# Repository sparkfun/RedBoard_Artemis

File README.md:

SparkFun RedBoard Artemis
============================

[*SparkFun RedBoard (DEV-15444)*](https://www.sparkfun.com/products/15444)

Think of the RedBoard Artemis as just another Arduino... That has BLE. And one meg of flash. And runs at less than 1mA. Oh, and it can run TensorFlow models. Ya, that too. The RedBoard Artemis takes the incredibly powerful Artemis module from SparkFun and wraps it up in an easy to use and familiar Uno footprint. We've written an Arduino core from scratch to make programming the Artemis as familiar as `Serial.begin(9600)`. Time-to-first-blink is less than five minutes.

The RedBoard Artemis has the improved power conditioning and USB to serial that we've refined over the years on our RedBoard line of products. A modern USB-C connector makes programming easy. A Qwiic connector makes I<sup>2</sup>C easy. The RedBoard Artemis is fully compatible with SparkFun's Arduino core and can be programmed easily under the Arduino IDE. We've exposed the JTAG connector for more advanced users who prefer to use the power and speed of professional tools. We've added a digital MEMS microphone for folks wanting to experiment with always-on voice commands with TensorFlow and machine learning. We've even added a convenient jumper to measure current consumption for low power testing.

With 1M flash and 384k RAM you'll have plenty of room for your sketches. The Artemis module runs at 48MHz with a 96MHz turbo mode available and with Bluetooth to boot!

The SparkFun RedBoard Artemis is a great platform to 'kick the tires' of this amazing module. If you're interesting in testing out the full capabilities of the SparkFun Artemis module or if you're looking for more compact solution, be sure to checkout our ATP and Nano versions of the Artemis line.

Repository Contents
-------------------
* **/Hardware** - Eagle design files (.brd, .sch)

Documentation
-------------------
* **[Hookup Guide for the RedBoard Artemis](https://learn.sparkfun.com/tutorials/hookup-guide-for-the-sparkfun-redboard-artemis)**
* **[Artemis Development with Arduino](https://learn.sparkfun.com/tutorials/artemis-development-with-arduino)**
* **[Ambiq Apollo3 SDK SetUp](https://learn.sparkfun.com/tutorials/using-sparkfun-edge-board-with-ambiq-apollo3-sdk)**
* **[Designing with the SparkFun Artemis](https://learn.sparkfun.com/tutorials/designing-with-the-sparkfun-artemis)**
* **[CH340E USB to serial IC Drivers](https://www.sparkfun.com/ch340)**

License Information
-------------------

This product is _**open source**_! 

Please review the LICENSE.md file for license information. 

If you have any questions or concerns on licensing, please contact techsupport@sparkfun.com.

Please use, reuse, and modify these files as you see fit. Please maintain attribution to SparkFun Electronics and release any derivative under the same license.

Distributed as-is; no warranty is given.

- Your friends at SparkFun.

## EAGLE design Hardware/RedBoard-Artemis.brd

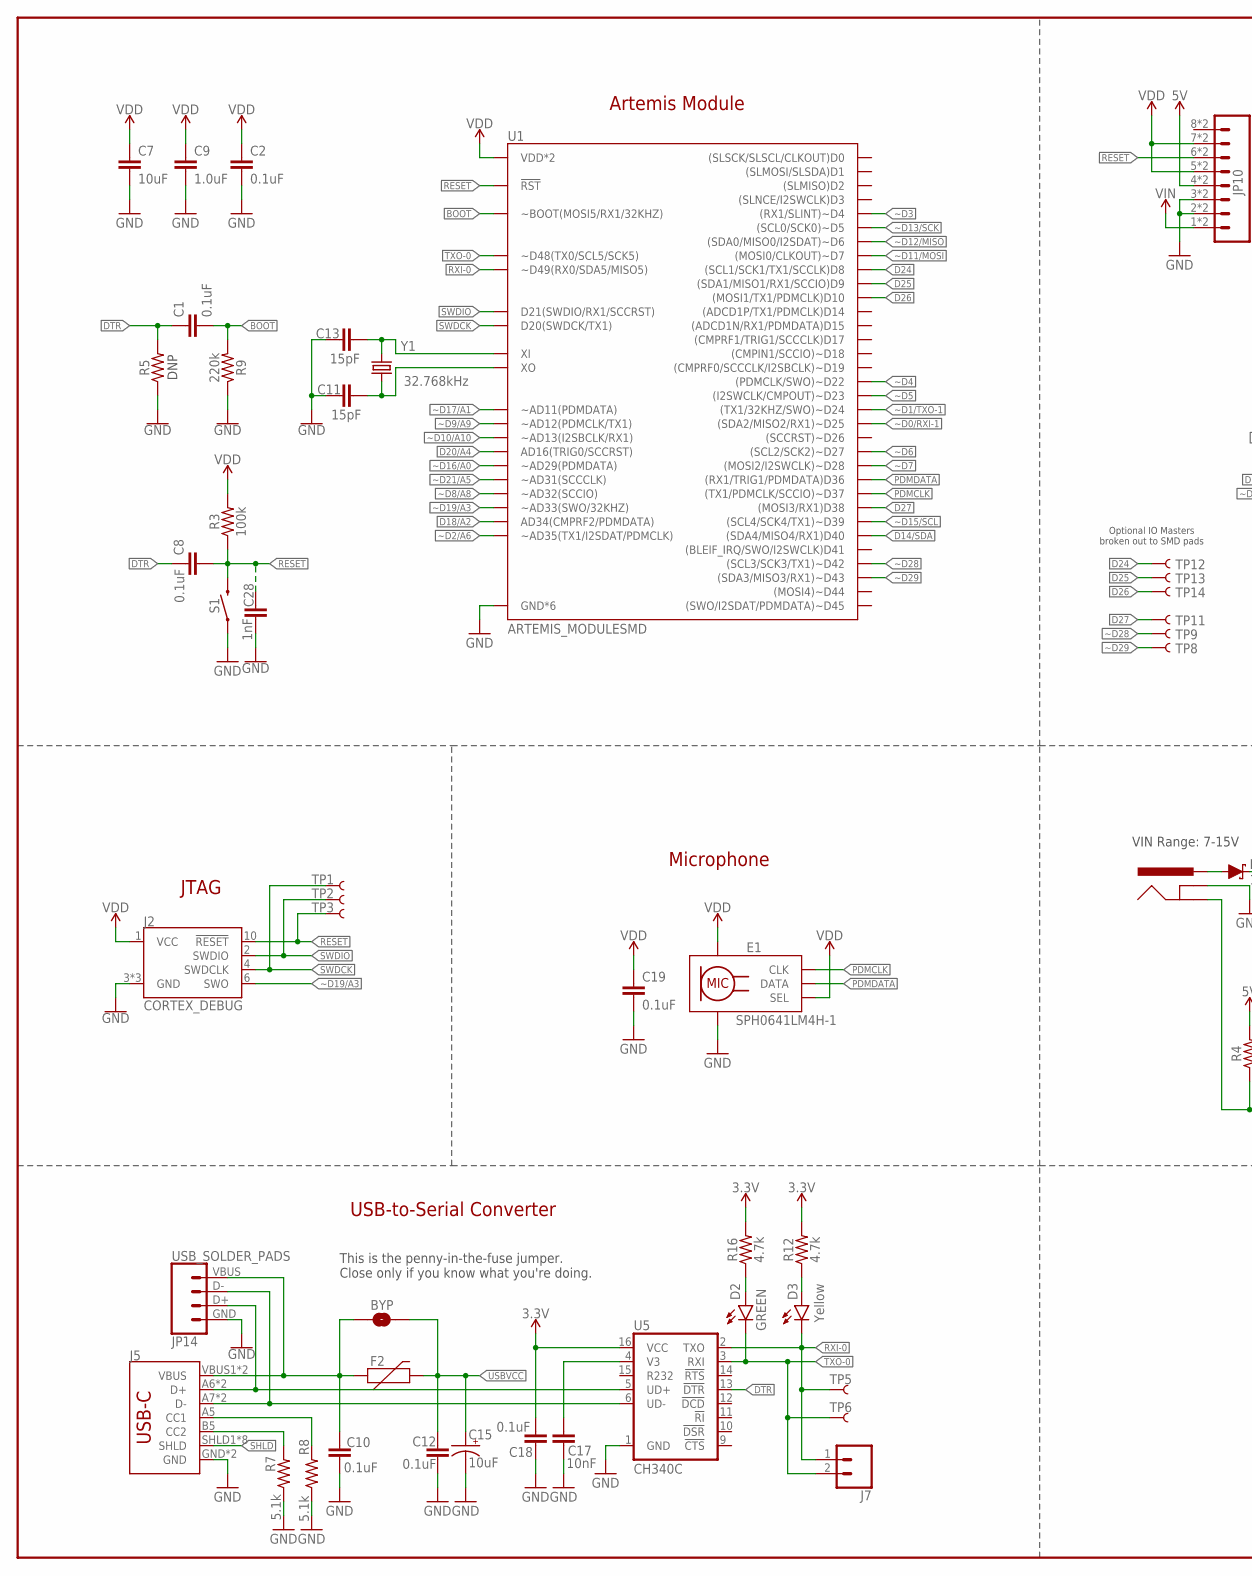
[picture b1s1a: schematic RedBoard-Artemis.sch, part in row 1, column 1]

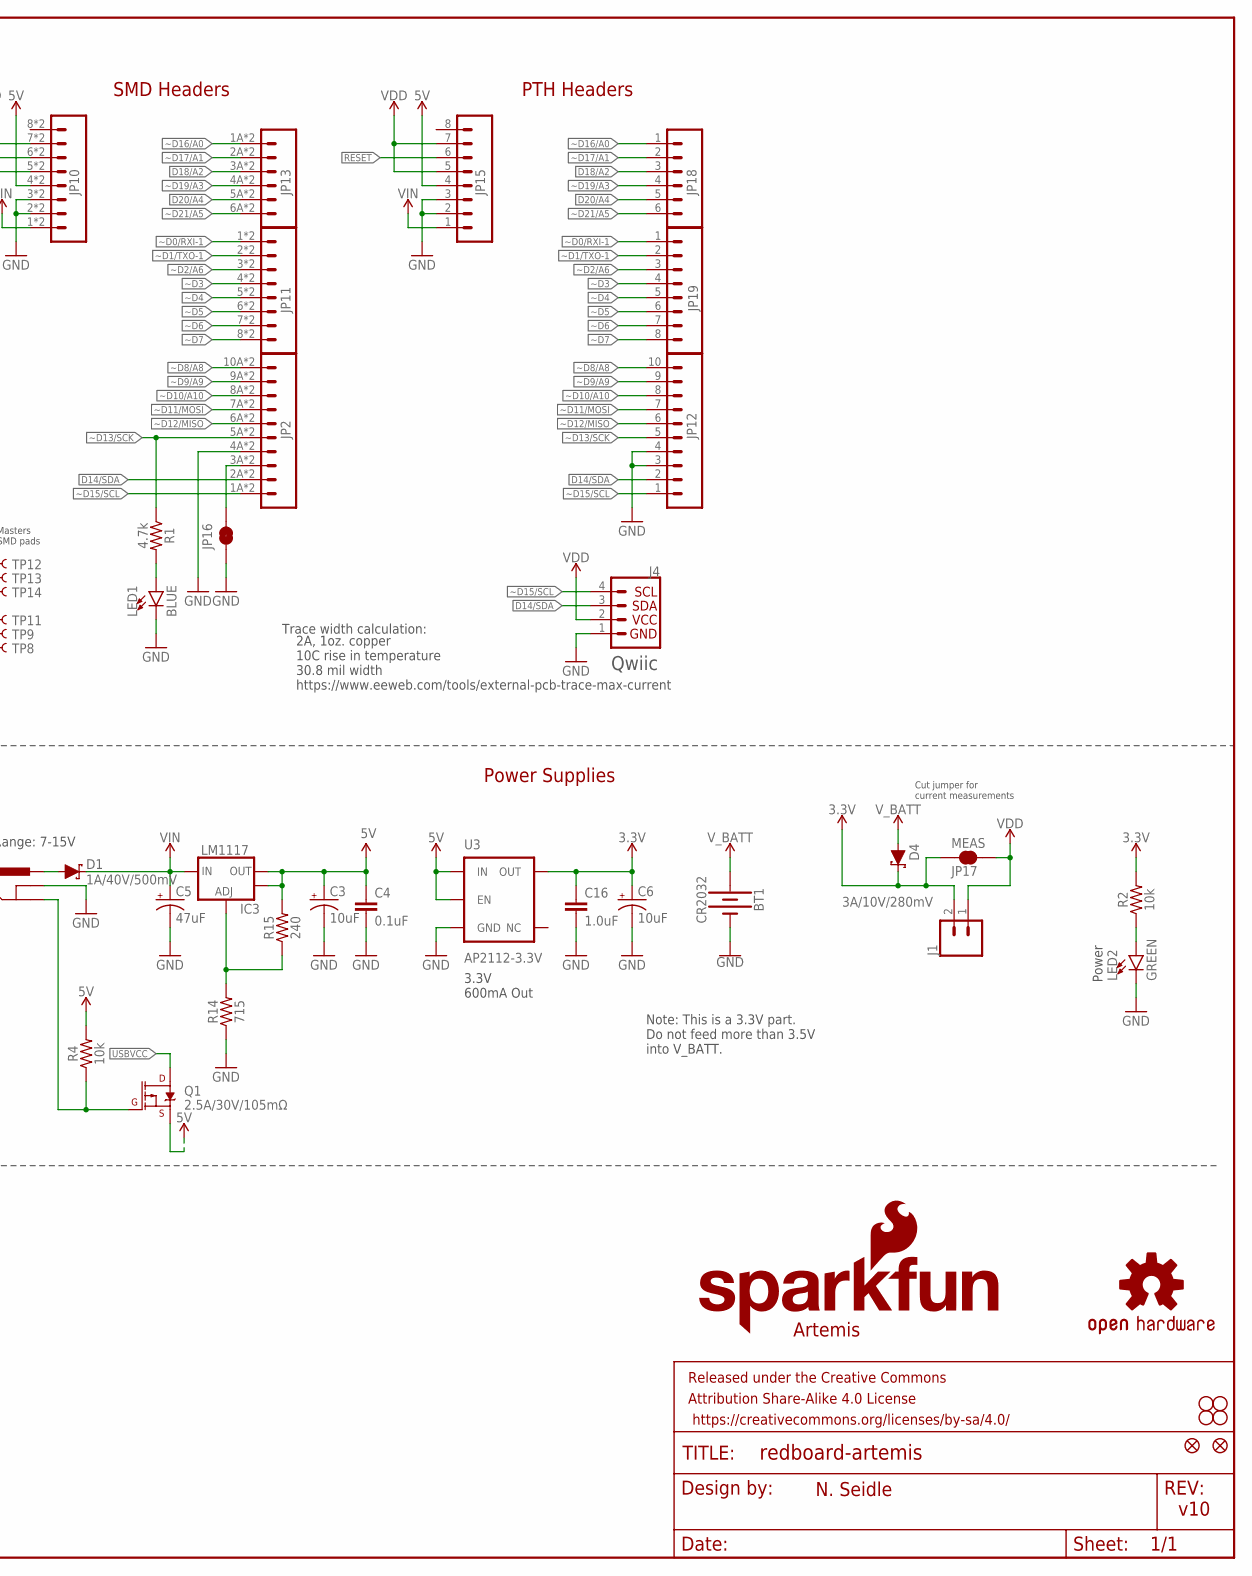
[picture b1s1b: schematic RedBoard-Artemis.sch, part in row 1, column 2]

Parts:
BT1: CR2032; BATTCON_20MM_4LEGS_OVERPASTE
BYP: JUMPER-SMT_2_NO_SILK; SMT-JUMPER_2_NO_SILK
C1, C2, C4, C8, C10, C12, C18, C19: 0.1uF; 0603
C3, C6, C15: 10uF; EIA3216
C5: 47uF; PANASONIC_D
C7: 10uF; 0603
C9, C16: 1.0uF; 0603
C11, C13: 15pF; 0603
C17: 10nF; 0603
C28: 1nF; 0603
D1: 1A/40V/500mV; SMA-DIODE
D2: GREEN; LED-1206
D3: Yellow; LED-1206
D4: 3A/10V/280mV; SOD-323
E1: SPH0641LM4H-1; SPH0641LM4H-1_MICROPHONE
F2: 6V/2A; 1210
FRAME3: FRAME-LEDGER; CREATIVE_COMMONS
IC3: LM1117; SOT223-ALT1
J1, J7: CONN_021X02_NO_SILK; 1X02_NO_SILK
J2: CORTEX_DEBUG; 2X5-PTH-1.27MM-NO_SILK
J3: POWER_JACKTOE; POWER_JACK_SMD_OVERPASTE_TOE
J4: QWIIC_CONNECTORJS-1MM; JST04_1MM_RA
J5: USB-C; USB-C-16P
JP1: SFE_LOGO_NAME.1_INCH; SFE_LOGO_NAME_.1
JP2: M10SMD_COMBO; 1X10_SMD_COMBINED
JP3, JP4, JP5, JP6: STAND-OFF
JP7: SFE_LOGO_FLAME.1_INCH; SFE_LOGO_FLAME_.1
JP8, JP9: FIDUCIAL1X2; FIDUCIAL-1X2
JP10: CONN_08SMD-COMBO-FEMALE_NC; 1X08_SMD_COMBINED_NC
JP11: JP11; 1X08_SMD_COMBINED_NC
JP12: M10NO_SILK; 1X10_NO_SILK
JP13: M06SMD-STRAIGHT-COMBO; 1X06_SMD_STRAIGHT_COMBO
JP14: USB_SOLDER_PADS; USB-SOLDER-PADS
JP15: M08NO_SILK; 1X08_NO_SILK@1
JP16: JUMPER-SMT_2_NC_TRACE_SILK; SMT-JUMPER_2_NC_TRACE_SILK
JP17: MEAS; SMT-JUMPER_2_NC_TRACE_SILK
JP18: M06NO_SILK; 1X06_NO_SILK@1
JP19: CONN_08NO_SILK_FEMALE_PTH; 1X08_NO_SILK
LED1: BLUE; LED-1206
LED2: GREEN; LED-1206
Q1: 2.5A/30V/105mΩ; SOT23-3
R1, R12, R16: 4.7k; 0603
R2, R4: 10k; 0603
R3: 100k; 0603
R5: 0603
R7, R8: 5.1k; 0603
R9: 220k; 0603
R14: 715; 0603
R15: 240; 0603
S1: MOMENTARY-SWITCH-SPST-SMD-5.2-TALL-REDUNDANT; TACTILE_SWITCH_SMD_5.2MM
TP1, TP2, TP3, TP5, TP6, TP8, TP9, TP11, TP12, TP13, TP14: TEST-POINT3X5; PAD.03X.05
U1: ARTEMIS_MODULESMD; ARTEMIS_FP
U3: AP2112-3.3V; SOT23-5
U5: CH340C; SO016
U$16: OSHW-LOGOS; OSHW-LOGO-S
Y1: 32.768kHz; CRYSTAL-SMD-3.2X1.5MM

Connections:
3.3V: C6.+, C16.1, C18.1, D4.C, J1.2, JP17.1, R2.2, R12.2, R16.2, U3.5 (OUT), U5.16 (VCC)
5V: C3.+, C4.1, IC3.2 (OUT), IC3.4 (OUT), JP10.4, JP10.4@2 (4), JP15.4, Q1.2 (S), R4.2, R15.2, U3.1 (IN), U3.3 (EN)
!DTR: C1.1, C8.1, R5.2, U5.13 (!DTR)
!RESET: C8.2, C28.1, J2.10 (!RESET), JP10.6, JP10.6@2 (6), JP15.6, R3.1, S1.3 (2), S1.4 (2), TP3.P$1, U1.~RST (!RST)
BOOT: C1.2, R9.2, U1.BOOT (~BOOT(MOSI5/RX1/32KHZ))
CC1: J5.A5 (CC1), R8.2
CC2: J5.B5 (CC2), R7.2
D14/SDA: J4.3, JP2.2A (2), JP2.2B (2), JP12.2, U1.D40 ((SDA4/MISO4/RX1)D40)
D18/A2: JP13.3A (3), JP13.3B (3), JP18.3, U1.AD34 (AD34(CMPRF2/PDMDATA))
D20/A4: JP13.5A (5), JP13.5B (5), JP18.5, U1.AD16 (AD16(TRIG0/SCCRST))
D24: TP12.P$1, U1.D8 ((SCL1/SCK1/TX1/SCCLK)D8)
D25: TP13.P$1, U1.D9 ((SDA1/MISO1/RX1/SCCIO)D9)
D26: TP14.P$1, U1.D10 ((MOSI1/TX1/PDMCLK)D10)
D27: TP11.P$1, U1.D38 ((MOSI3/RX1)D38)
D+: J5.A6 (D+), J5.B6 (D+), JP14.D+ (3), U5.5 (UD+)
D-: J5.A7 (D-), J5.B7 (D-), JP14.D- (2), U5.6 (UD-)
GND: BT1.2 (-), C2.1, C3.-, C4.2, C5.-, C6.-, C7.2, C9.2, C10.2, C11.1, C12.2, C13.1, C15.-, C16.2, C17.2, C18.2, C19.2, C28.2, E1.3 (GND), E1.6 (GND), E1.7 (GND), E1.8 (GND), J2.3 (GND), J2.5 (GND), J2.9 (GND), J3.GND (GNDBREAK), J4.1, J5.GND, J5.GND2 (GND), JP2.4A (4), JP2.4B (4), JP10.2, JP10.2@2 (2), JP10.3, JP10.3@2 (3), JP12.3, JP12.4, JP14.GND (4), JP15.2, JP15.3, JP16.1, LED1.C, LED2.C, R5.1, R7.1, R8.1, R9.1, R14.1, S1.1, S1.2 (1), U1.GND@1 (GND*6), U1.GND@22 (GND*6), U1.GND@38 (GND*6), U1.GND@39 (GND*6), U1.GND@47 (GND*6), U1.GND@59 (GND*6), U3.2 (GND), U5.1 (GND)
INSERT: J3.P$4 (GND), Q1.1 (G), R4.1
unnamed: LED1.A, R1.2
unnamed: LED2.A, R2.1
unnamed: D2.A, R16.1
unnamed: C17.1, U5.4 (V3)
unnamed: C11.2, U1.XO, Y1.P$2 (2)
unnamed: C13.2, U1.XI, Y1.P$1 (1)
unnamed: D3.A, R12.1
unnamed: JP2.3A (3), JP2.3B (3), JP16.2
unnamed: IC3.1 (ADJ), R14.2, R15.1
PDMCLK: E1.4 (CLK), U1.~D37 ((TX1/PDMCLK/SCCIO)~D37)
PDMDATA: E1.1 (DATA), U1.D36 ((RX1/TRIG1/PDMDATA)D36)
PWRIN: D1.A, J3.VIN0 (PWR)
RXI-0: D3.C, J7.1, TP5.P$1, U1.RXI-0 (~D49(RX0/SDA5/MISO5)), U5.2 (TXO)
SHLD: J5.SHLD1 (SHLD), J5.SHLD2 (SHLD), J5.SHLD3 (SHLD), J5.SHLD4 (SHLD), J5.SHLD5 (SHLD), J5.SHLD6 (SHLD), J5.SHLD7 (SHLD), J5.SHLD8 (SHLD)
SWDCK: J2.4 (SWDCLK), TP1.P$1, U1.SWDCK (D20(SWDCK/TX1))
SWDIO: J2.2 (SWDIO), TP2.P$1, U1.SWDIO (D21(SWDIO/RX1/SCCRST))
TXO-0: D2.C, J7.2, TP6.P$1, U1.TXO-0 (~D48(TX0/SCL5/SCK5)), U5.3 (RXI)
USBVCC: BYP.2, C12.1, C15.+, F2.2, Q1.3 (D)
VDD: C2.2, C7.1, C9.1, C19.1, E1.2 (SEL), E1.5 (VDD), J1.1, J2.1 (VCC), J4.2, JP10.5, JP10.5@2 (5), JP10.7, JP10.7@2 (7), JP15.5, JP15.7, JP17.2, R3.2, U1.VDD@36 (VDD*2), U1.VDD@37 (VDD*2)
VIN: C5.+, D1.C, IC3.3 (IN), JP10.1, JP10.1@2 (1), JP15.1
VUSB: BYP.1, C10.1, F2.1, J5.VBUS1 (VBUS), J5.VBUS2 (VBUS), JP14.VBUS (1)
V_BATT: BT1.1 (+), D4.A
~D0/RXI-1: JP11.1, JP11.1@2 (1), JP19.1, U1.~D25 ((SDA2/MISO2/RX1)~D25)
~D1/TXO-1: JP11.2, JP11.2@2 (2), JP19.2, U1.~D24 ((TX1/32KHZ/SWO)~D24)
~D2/A6: JP11.3, JP11.3@2 (3), JP19.3, U1.~AD35 (~AD35(TX1/I2SDAT/PDMCLK))
~D3: JP11.4, JP11.4@2 (4), JP19.4, U1.~D4 ((RX1/SLINT)~D4)
~D4: JP11.5, JP11.5@2 (5), JP19.5, U1.~D22 ((PDMCLK/SWO)~D22)
~D5: JP11.6, JP11.6@2 (6), JP19.6, U1.~D23 ((I2SWCLK/CMPOUT)~D23)
~D6: JP11.7, JP11.7@2 (7), JP19.7, U1.~D27 ((SCL2/SCK2)~D27)
~D7: JP11.8, JP11.8@2 (8), JP19.8, U1.~D28 ((MOSI2/I2SWCLK)~D28)
~D8/A8: JP2.10A (10), JP2.10B (10), JP12.10, U1.~AD32 (~AD32(SCCIO))
~D9/A9: JP2.9A (9), JP2.9B (9), JP12.9, U1.~AD12 (~AD12(PDMCLK/TX1))
~D10/A10: JP2.8A (8), JP2.8B (8), JP12.8, U1.~AD13 (~AD13(I2SBCLK/RX1))
~D11/MOSI: JP2.7A (7), JP2.7B (7), JP12.7, U1.D7 ((MOSI0/CLKOUT)~D7)
~D12/MISO: JP2.6A (6), JP2.6B (6), JP12.6, U1.~D6 ((SDA0/MISO0/I2SDAT)~D6)
~D13/SCK: JP2.5A (5), JP2.5B (5), JP12.5, R1.1, U1.~D5 ((SCL0/SCK0)~D5)
~D15/SCL: J4.4, JP2.1A (1), JP2.1B (1), JP12.1, U1.~D39 ((SCL4/SCK4/TX1)~D39)
~D16/A0: JP13.1A (1), JP13.1B (1), JP18.1, U1.~AD29 (~AD29(PDMDATA))
~D17/A1: JP13.2A (2), JP13.2B (2), JP18.2, U1.~AD11 (~AD11(PDMDATA))
~D19/A3: J2.6 (SWO), JP13.4A (4), JP13.4B (4), JP18.4, U1.~AD33/SWO (~AD33(SWO/32KHZ))
~D21/A5: JP13.6A (6), JP13.6B (6), JP18.6, U1.~AD31 (~AD31(SCCCLK))
~D28: TP9.P$1, U1.~D42 ((SCL3/SCK3/TX1)~D42)
~D29: TP8.P$1, U1.~D43 ((SDA3/MISO3/RX1)~D43)

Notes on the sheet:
Artemis
USB-to-Serial Converter
N. Seidle
v10
This is the penny-in-the-fuse jumper. Close only if you know what you're doing.
Optional IO Masters broken out to SMD pads
Artemis Module
SMD Headers
DNP
PTH Headers
VIN Range: 7-15V
3.3V 600mA Out
Cut jumper for current measurements
Power Supplies
Note: This is a 3.3V part. Do not feed more than 3.5V into V_BATT.
Power
Microphone
Qwiic
Trace width calculation:
2A, 1oz. copper 10C rise in temperature 30.8 mil width https://www.eeweb.com/tools/external-pcb-trace-max-current
JTAG

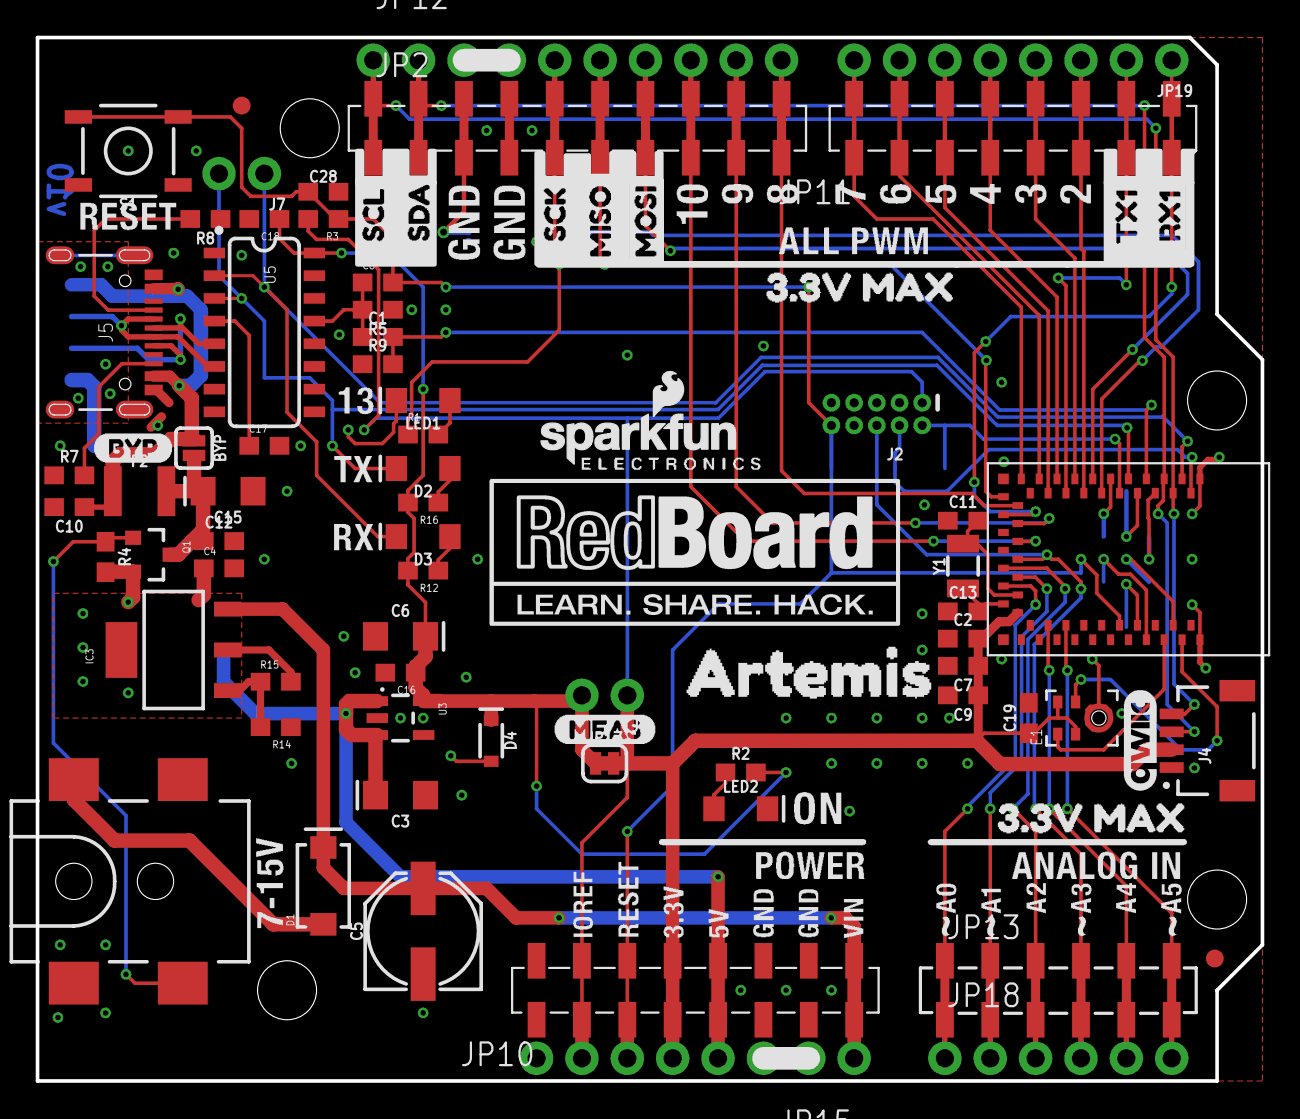
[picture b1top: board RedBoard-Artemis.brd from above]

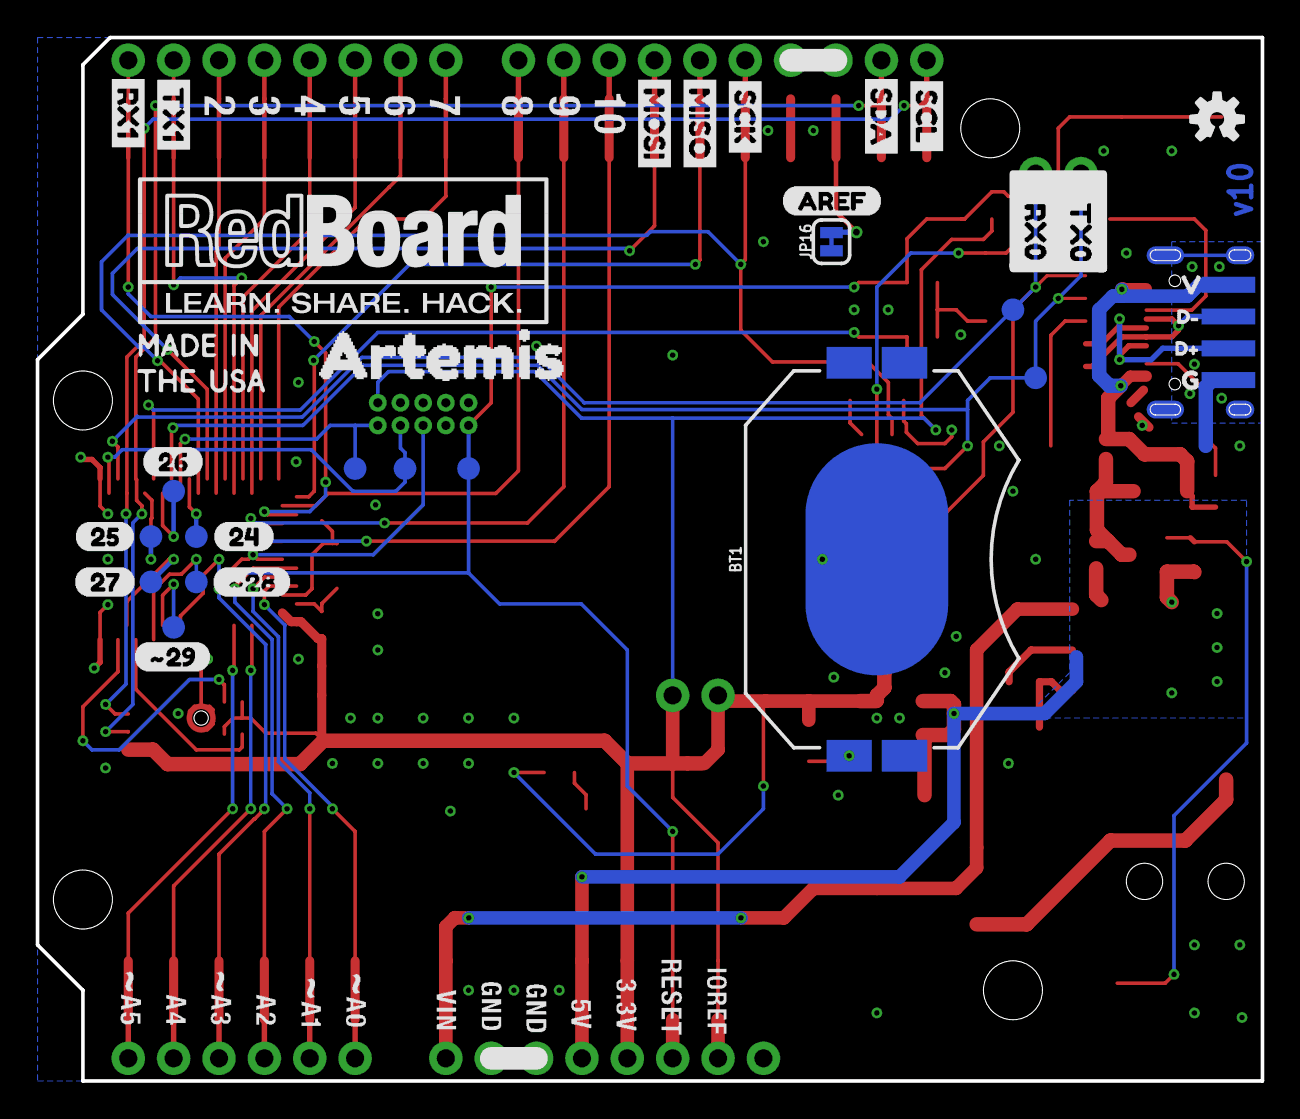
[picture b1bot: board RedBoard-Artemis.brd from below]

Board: 2 copper layers, 68.6 x 58.4 mm, 122 parts (38 on the bottom side), 61 nets.

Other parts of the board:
FRAME2: FRAME-LETTERNO_PACKAGE; DUMMY
U$1, U$18: SCL1
U$2: D#3
U$3, U$22: SDA0
U$4: MADEINUSA#PNG
U$9: QWIIC_COPYRIGHT_SMALL
U$10: D#4
U$11: G1
U$12: V0
U$13, U$67: 3#3V_MAX2
U$14, U$15: ARTEMIS0
U$17: #284
U$19: #295
U$20: AREF2
U$21: 240
U$23: 251
U$24: 262
U$25: 273
U$26, U$50: SCK9
U$27, U$47: MISO8
U$28, U$48: MOSI7
U$29, U$72: TX10
U$30, U$71: RX11
U$49: RX01
U$53: TX00
U$68: BYP0
U$70: MEAS3

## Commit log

2019-07-02 Move measurement PTH from under CR2032.
2019-07-02 Rename silk to RedBoard. Change version to v10.
2019-07-02 Silk adjust
2019-07-02 Remove diode from 3.3V rail. Move MEAS jumper.
2019-07-02 Add PTH connectors to edges of board.
2019-07-03 Add bottom silk indicators. Move MEAS jumper.
2019-07-03 Approved DRC errors
2019-07-03 Adding production panels
2019-07-03 Adding designed by text

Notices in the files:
parts and their libraries:
SparkFun-Aesthetics: Licensing: CC v3.0 Share-Alike You are welcome to use this library for commercial purposes.
SparkFun-Aesthetics: Released under the Creative Commons Attribution Share-Alike 4.0 License
SparkFun-Aesthetics: https://creativecommons.org/licenses/by-sa/4.0
